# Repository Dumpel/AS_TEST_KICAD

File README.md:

# ml_multigate

Test repository for Kicad project with multigate compoments

## Content

U1 - 4 out of 5 units placed to sch, synced to PCB

U2 - all 5 units placed to sch, synced to PCB

Power and ground symbols, wires connected

## Expected results

BOM with two components U1, U2, type - IC, value - 4001

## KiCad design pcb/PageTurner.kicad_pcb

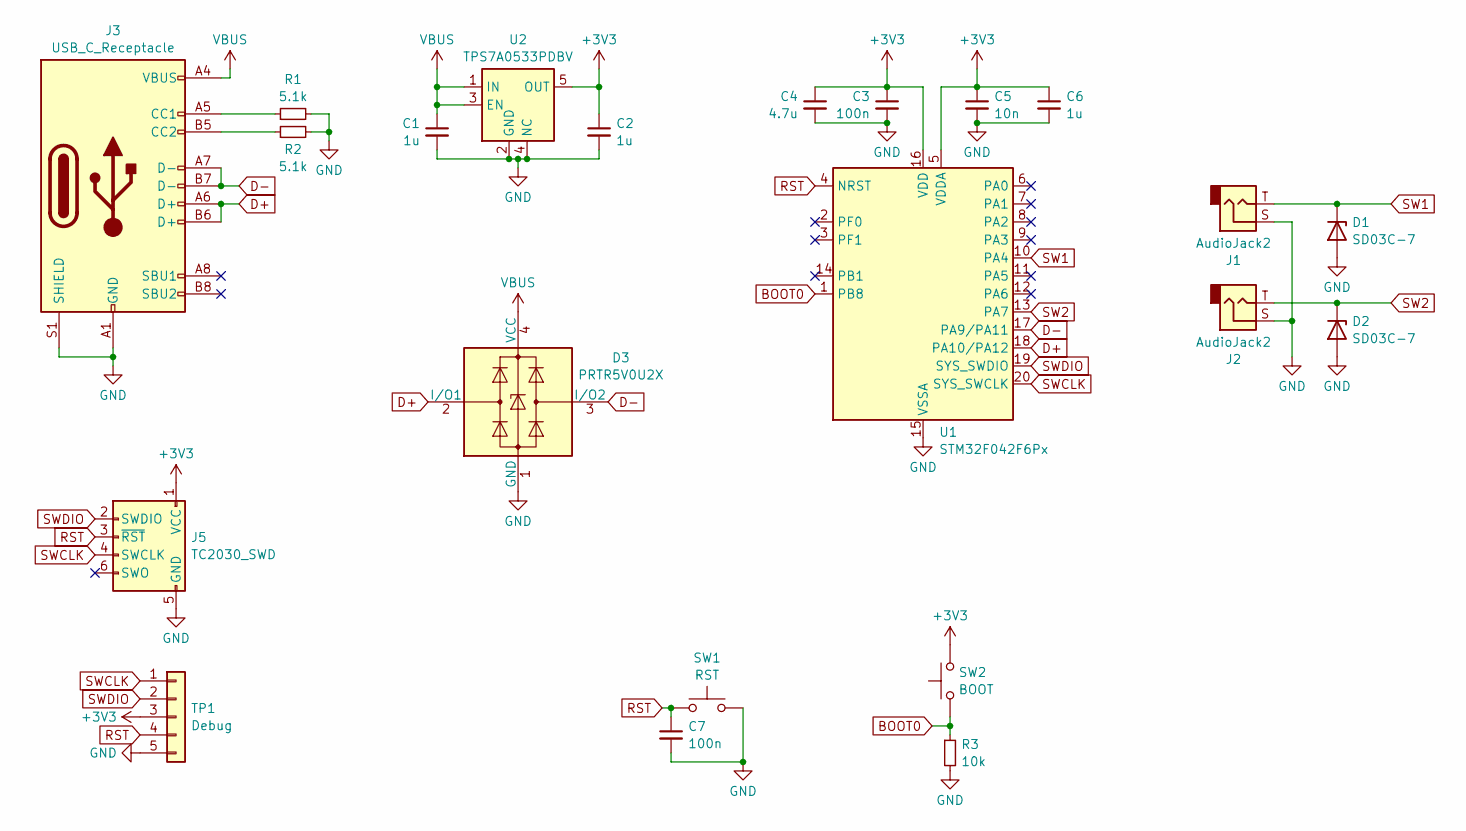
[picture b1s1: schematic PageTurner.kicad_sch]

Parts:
C1, C2, C6: 1u; C_0603_1608Metric_Pad1.08x0.95mm_HandSolder
C3, C7: 100n; C_0603_1608Metric_Pad1.08x0.95mm_HandSolder
C4: 4.7u; C_0603_1608Metric_Pad1.08x0.95mm_HandSolder
C5: 10n; C_0603_1608Metric_Pad1.08x0.95mm_HandSolder
D1, D2: SD03C-7; D_SOD-323_HandSoldering; Manufacturer Part Number SD03C-7
D3: PRTR5V0U2X; SOT-143; Manufacturer Part Number PRTR5V0U2X,215
J1, J2: AudioJack2; Jack_6.35mm_Neutrik_NJ2FD-V_Vertical; Manufacturer Part Number NJ2FD-V
J3: USB_C_Receptacle; USB_C_Receptacle_GCT_USB_4145; Manufacturer Part Number DX07S024WJ3R400
J5: TC2030_SWD; Tag-Connect_TC2030-IDC-NL_2x03_P1.27mm_Vertical
R1, R2: 5.1k; R_0603_1608Metric_Pad0.98x0.95mm_HandSolder
R3: 10k; R_0603_1608Metric_Pad0.98x0.95mm_HandSolder
SW1: RST; SW_SPST_B3U-1000P-B; Manufacturer Part Number B3U-1100P-B
SW2: BOOT; SW_SPST_B3U-1000P-B; Manufacturer Part Number B3U-1100P-B
TP1: Debug; PinHeader_1x05_P2.00mm_Vertical
U1: STM32F042F6Px; TSSOP-20_4.4x6.5mm_P0.65mm; Manufacturer Part Number STM32F042F6P6TR
U2: TPS7A0533PDBV; SOT-23-5; Manufacturer Part Number TPS7A0333PDBVR

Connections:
+3V3: C2.1, C3.1, C4.1, C5.1, C6.1, J5.1 (VCC), SW2.2, TP1.3, U1.5 (VDDA), U1.16 (VDD), U2.5 (OUT)
BOOT0: R3.1, SW2.1, U1.1 (PB8)
D+: D3.2 (I/O1), J3.A6 (D+), J3.B6 (D+), U1.18 (PA10/PA12)
D-: D3.3 (I/O2), J3.A7 (D-), J3.B7 (D-), U1.17 (PA9/PA11)
GND: C1.2, C2.2, C3.2, C4.2, C5.2, C6.2, C7.2, D1.2 (A), D2.2 (A), D3.1 (GND), J1.S, J2.S, J3.A1 (GND), J3.A12 (GND), J3.B1 (GND), J3.B12 (GND), J3.S1 (SHIELD), J5.5 (GND), R1.2, R2.2, R3.2, SW1.2, TP1.5, U1.15 (VSSA), U2.2 (GND), U2.4 (NC)
unnamed: J3.A5 (CC1), R1.1
unnamed: J3.B5 (CC2), R2.1
RST: C7.1, J5.3 (~RST), SW1.1, TP1.4, U1.4 (NRST)
SW1: D1.1 (K), J1.T, U1.10 (PA4)
SW2: D2.1 (K), J2.T, U1.13 (PA7)
SWCLK: J5.4 (SWCLK), TP1.1, U1.20 (SYS_SWCLK)
SWDIO: J5.2 (SWDIO), TP1.2, U1.19 (SYS_SWDIO)
VBUS: C1.1, D3.4 (VCC), J3.A4 (VBUS), J3.A9 (VBUS), J3.B4 (VBUS), J3.B9 (VBUS), U2.1 (IN), U2.3 (EN)

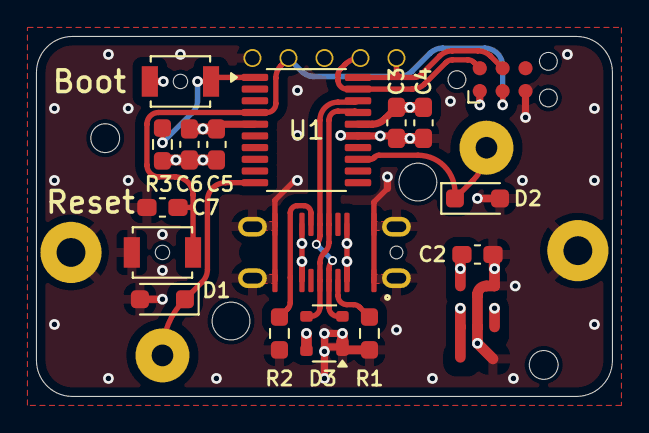
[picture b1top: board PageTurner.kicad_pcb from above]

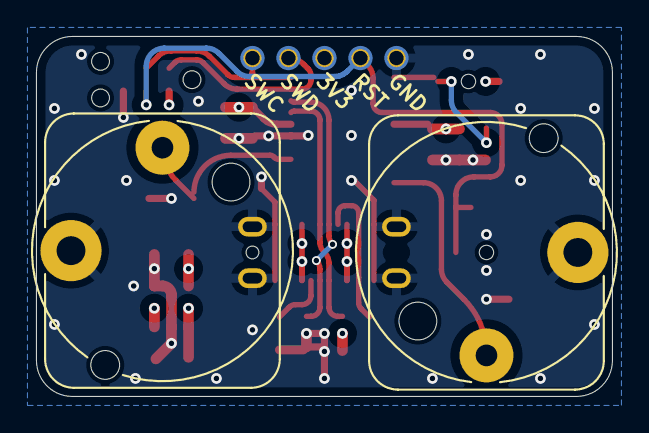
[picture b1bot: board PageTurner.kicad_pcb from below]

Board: 4 copper layers, 32.0 x 20.0 mm, 20 parts (3 on the bottom side), 13 nets.
